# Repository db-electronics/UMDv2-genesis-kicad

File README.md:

# UMDv2-genesis-kicad
UMDv2 Genesis Cartridge Adapter

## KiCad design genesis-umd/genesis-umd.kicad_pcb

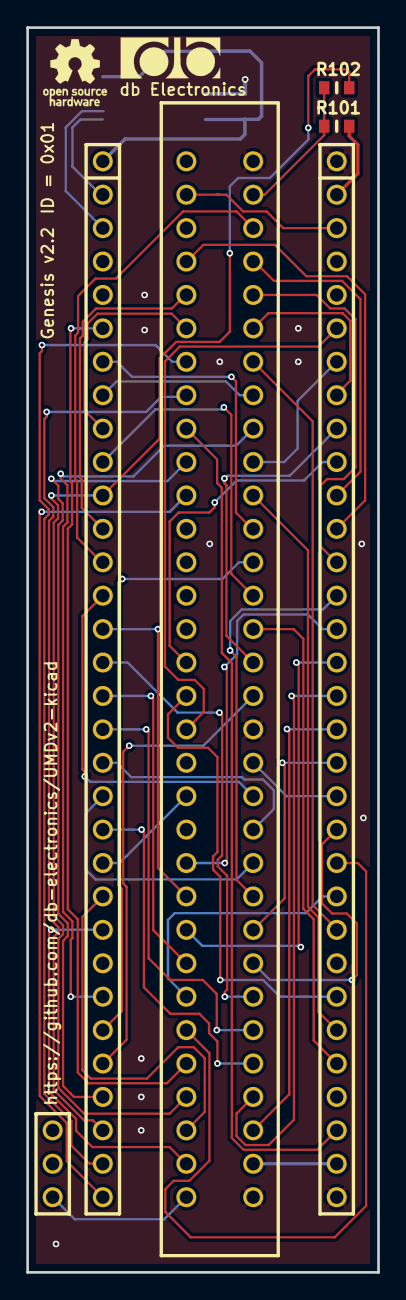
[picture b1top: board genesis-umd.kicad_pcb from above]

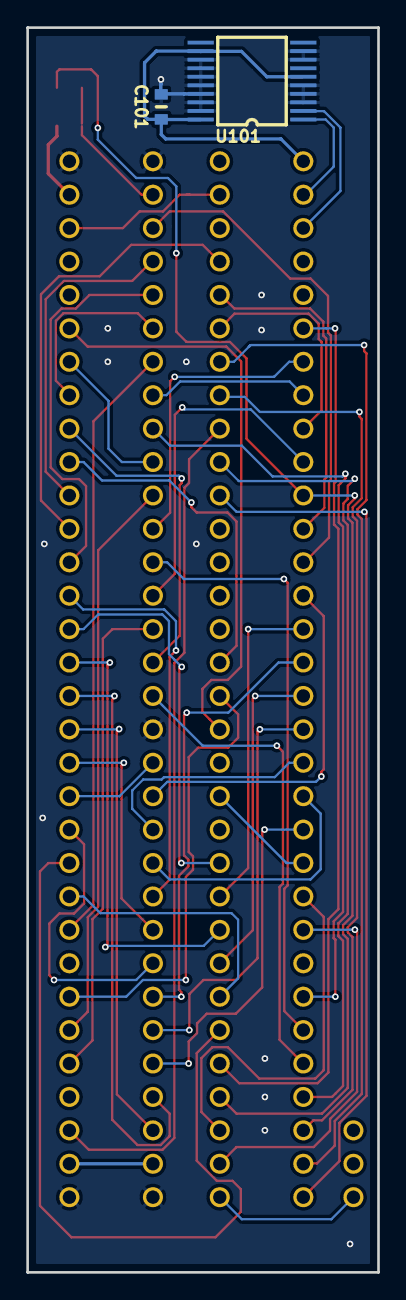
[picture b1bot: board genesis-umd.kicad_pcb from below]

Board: 2 copper layers, 26.7 x 94.6 mm, 6 parts (2 on the bottom side), 58 nets.

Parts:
C101: 0.1uF/50V; 0603
CON101: UMDv2-CONN; UMD-CONN-DIP64
CON102: GENESIS-CONN
R101, R102: 0; 0603
U101: MCP23008T-E_SS; SSOP-20

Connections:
+3V3: C101.1, CON101.1, U101.6, U101.12, U101.20
/5V_0: CON101.63, R101.2
/5V_1: CON101.34, CON102.A31
/A1: CON101.28, CON102.A17
/A2: CON101.37, CON102.A15
/A3: CON101.27, CON102.A13
/A4: CON101.38, CON102.A11
/A5: CON101.26, CON102.A9
/A6: CON101.41, CON102.A7
/A7: CON101.52, CON102.A5
/A8: CON101.13, CON102.A3
/A9: CON101.53, CON102.B4
/A10: CON101.12, CON102.B5
/A11: CON101.54, CON102.A4
/A12: CON101.57, CON102.A6
/A13: CON101.8, CON102.A8
/A14: CON101.58, CON102.A10
/A15: CON101.7, CON102.A12
/A16: CON101.10, CON102.A14
/A17: CON101.56, CON102.A16
/A18: CON101.9, CON102.B6
/A19: CON101.31, CON102.B7
/A20: CON101.30, CON102.B8
/A21: CON101.35, CON102.B9
/A22: CON101.29, CON102.B10
/A23: CON101.32, CON102.B11
/D0: CON101.14, CON102.A20
/D1: CON101.51, CON102.A23
/D2: CON101.16, CON102.A26
/D3: CON101.48, CON102.A29
/D4: CON101.21, CON102.A28
/D5: CON101.44, CON102.A25
/D6: CON101.20, CON102.A22
/D7: CON101.45, CON102.A19
/D8: CON101.19, CON102.A21
/D9: CON101.46, CON102.A24
/D10: CON101.18, CON102.A27
/D11: CON101.47, CON102.A30
/D12: CON101.17, CON102.B25
/D13: CON101.49, CON102.B24
/D14: CON101.15, CON102.B23
/D15: CON101.50, CON102.B22
/SCL: CON101.2, U101.1
/SDA: CON101.3, U101.2
/~ASEL~: CON101.42, CON102.B26
/~AS~: CON101.59, CON102.B18
/~CART~: CON101.67, CON102.B32
/~CE~: CON101.39, CON102.B17
/~DTACK~: CON101.22, CON102.B20
/~LWR~: CON101.6, CON102.B28
/~M3~: CON101.23, CON102.B30
/~MRES~: CON101.62, CON102.B2
/~RD~: CON101.55, CON102.B16
/~TIME~: CON101.24, CON102.B31
/~VRES~: CON101.43, CON102.B27
/~WR~: CON101.11, CON102.B29, R102.2
GND: C101.2, CON101.33, CON101.64, CON102.A1, CON102.A18, CON102.A32, U101.3, U101.4, U101.5, U101.8, U101.9, U101.13, U101.14, U101.15, U101.16, U101.17, U101.18, U101.19
unnamed: CON102.A2, R101.1, R102.1

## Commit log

2020-02-11 moved Genesis adpater to its own repo as a submodule of main UMDv2 project
2020-02-11 fixed folder structure for KiCad - project files in their own dir
2020-02-12 changed ID on board to 0x01, realized that ID 0x00 should be reserved for undefined
2020-03-16 corrected nRST tied permanently low on MCP23008
2020-03-21 added OSHWA markings for v2.2 release

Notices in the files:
genesis-umd/genesis-umd.kicad_pcb:
Licensed Under CERN OHL v.1.2
